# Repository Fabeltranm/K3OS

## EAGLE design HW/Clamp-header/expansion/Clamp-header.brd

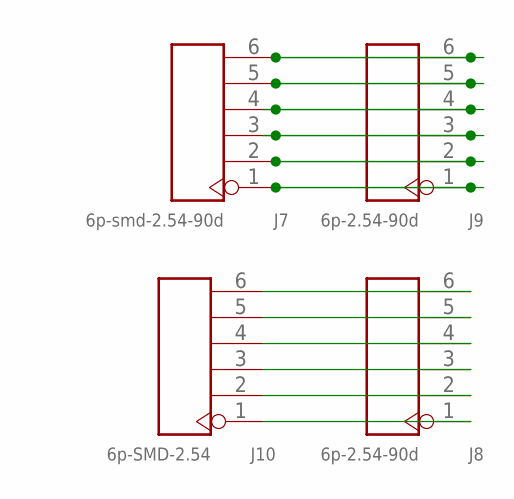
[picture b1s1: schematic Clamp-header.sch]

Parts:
J7: 6p-smd-2.54-90d; H6-SMD-MALE-2.54-90D
J8, J9: 6p-2.54-90d; H6-2.54-90D-FEMALE
J10: 6p-SMD-2.54; H6-SMD-2.54

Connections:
unnamed: J7.6, J9.6
unnamed: J7.5, J9.5
unnamed: J7.4, J9.4
unnamed: J7.3, J9.3
unnamed: J7.2, J9.2
unnamed: J7.1, J9.1
unnamed: J8.6, J10.6
unnamed: J8.5, J10.5
unnamed: J8.4, J10.4
unnamed: J8.3, J10.3
unnamed: J8.2, J10.2
unnamed: J8.1, J10.1

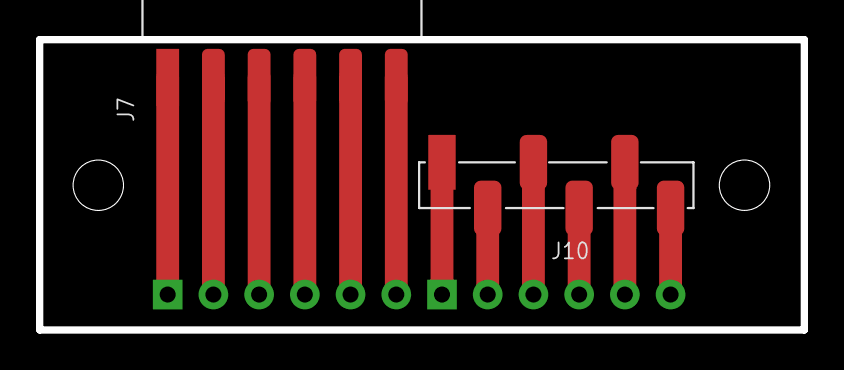
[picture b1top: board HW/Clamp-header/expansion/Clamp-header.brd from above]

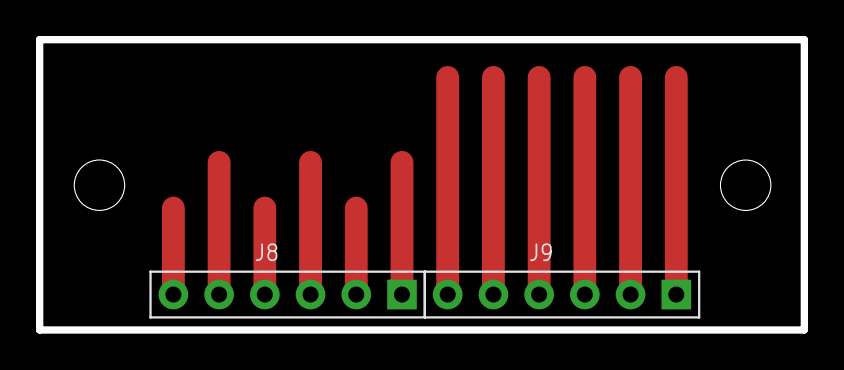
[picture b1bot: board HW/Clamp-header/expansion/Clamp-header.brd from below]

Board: 2 copper layers, 42.5 x 16.1 mm, 4 parts (2 on the bottom side), 12 nets.

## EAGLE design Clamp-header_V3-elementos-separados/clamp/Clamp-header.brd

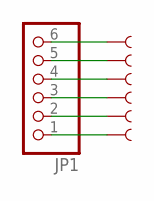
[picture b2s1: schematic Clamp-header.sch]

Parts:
JP1: PINHD-1X6/90; 1X06/90
U$1, U$2, U$3, U$5, U$6, U$7: SEWTAP1; SEWTAP

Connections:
unnamed: JP1.6, U$3.1
unnamed: JP1.5, U$6.1
unnamed: JP1.4, U$7.1
unnamed: JP1.3, U$1.1
unnamed: JP1.2, U$5.1
unnamed: JP1.1, U$2.1

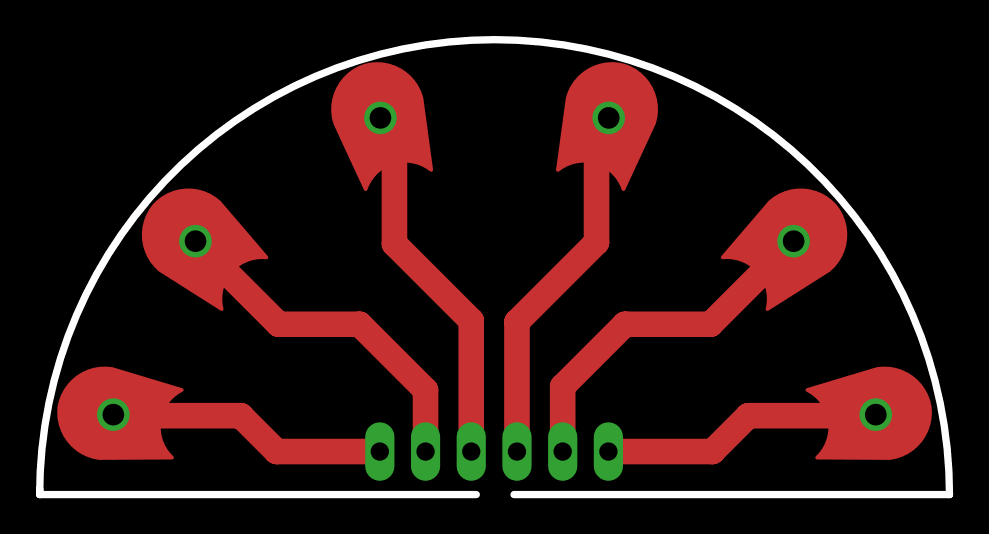
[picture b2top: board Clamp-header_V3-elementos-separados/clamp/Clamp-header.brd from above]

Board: 2 copper layers, 50.5 x 25.3 mm, 7 parts (1 on the bottom side), 6 nets.

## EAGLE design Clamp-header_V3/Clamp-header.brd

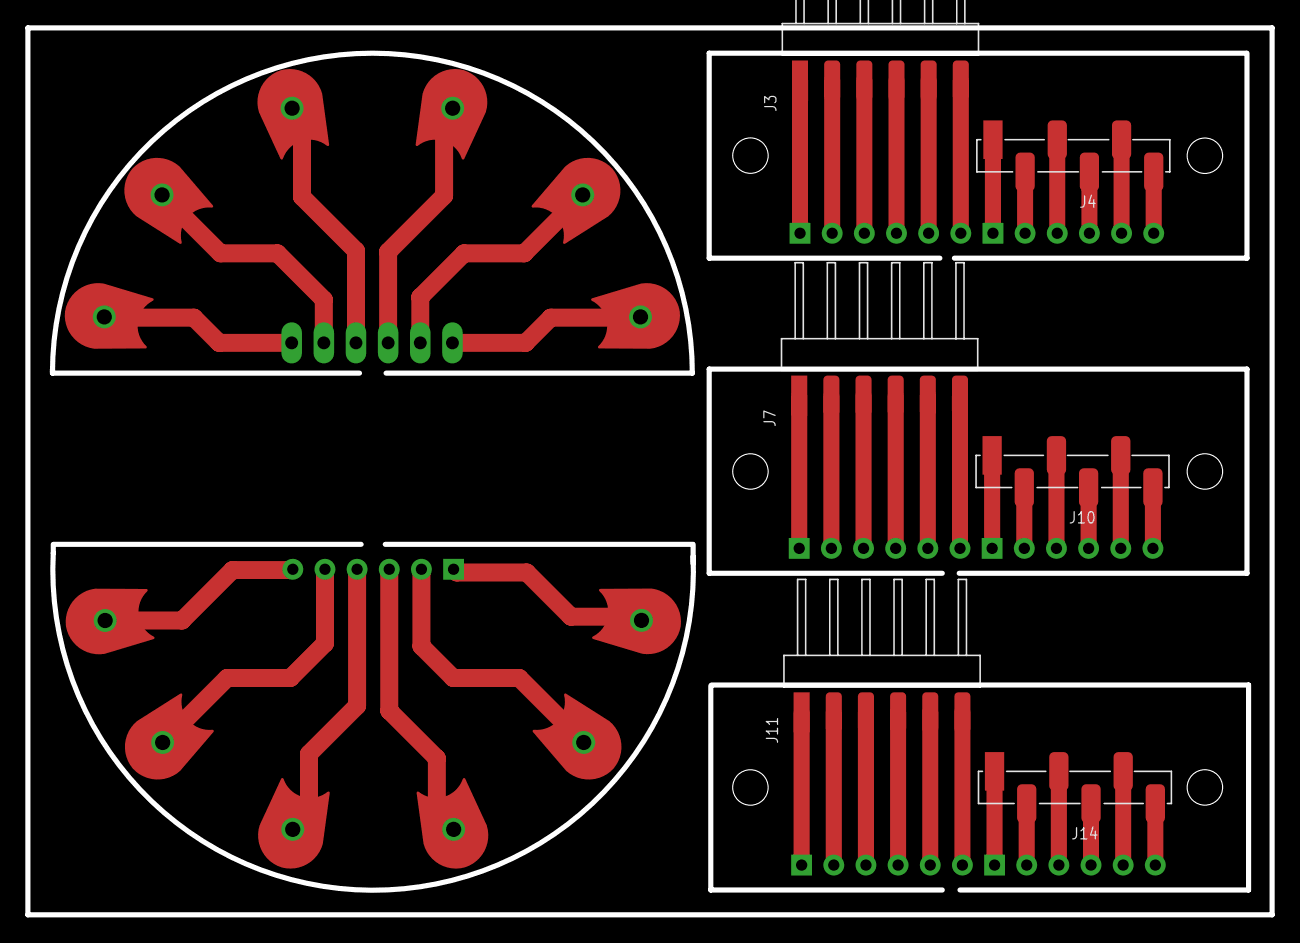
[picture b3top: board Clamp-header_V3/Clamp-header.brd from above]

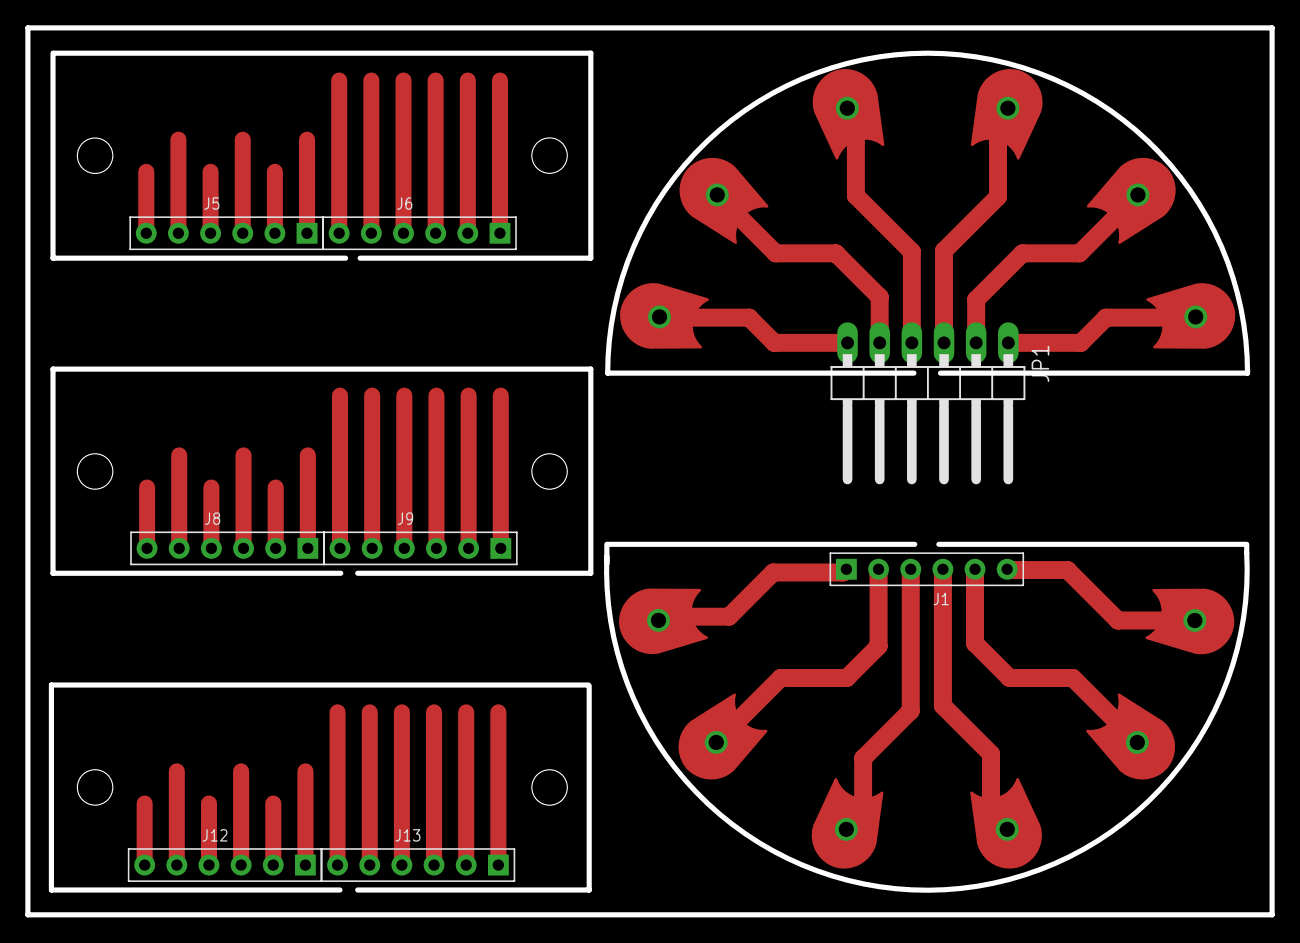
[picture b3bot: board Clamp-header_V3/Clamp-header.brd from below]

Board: 2 copper layers, 98.3 x 70.1 mm, 26 parts (8 on the bottom side), 48 nets.

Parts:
J1, J5, J6, J8, J9, J12, J13: 6p-2.54-90d; H6-2.54-90D-FEMALE
J3, J7, J11: 6p-smd-2.54-90d; H6-SMD-MALE-2.54-90D
J4, J10, J14: 6p-SMD-2.54; H6-SMD-2.54
JP1: 1X06/90
U$1, U$2, U$3, U$4, U$5, U$6, U$7, U$35, U$37, U$39, U$41, U$51: SEWTAP1; SEWTAP

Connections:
unnamed: J1.6, U$51.1
unnamed: J1.5, U$41.1
unnamed: J1.4, U$35.1
unnamed: J1.3, U$37.1
unnamed: J1.2, U$39.1
unnamed: J1.1, U$4.1
unnamed: JP1.6, U$3.1
unnamed: JP1.5, U$6.1
unnamed: JP1.4, U$7.1
unnamed: JP1.3, U$1.1
unnamed: JP1.2, U$5.1
unnamed: JP1.1, U$2.1
unnamed: J3.6, J6.6
unnamed: J3.5, J6.5
unnamed: J3.4, J6.4
unnamed: J3.3, J6.3
unnamed: J3.2, J6.2
unnamed: J3.1, J6.1
unnamed: J4.6, J5.6
unnamed: J4.5, J5.5
unnamed: J4.4, J5.4
unnamed: J4.3, J5.3
unnamed: J4.2, J5.2
unnamed: J4.1, J5.1
unnamed: J7.6, J9.6
unnamed: J7.5, J9.5
unnamed: J7.4, J9.4
unnamed: J7.3, J9.3
unnamed: J7.2, J9.2
unnamed: J7.1, J9.1
unnamed: J8.6, J10.6
unnamed: J8.5, J10.5
unnamed: J8.4, J10.4
unnamed: J8.3, J10.3
unnamed: J8.2, J10.2
unnamed: J8.1, J10.1
unnamed: J11.6, J13.6
unnamed: J11.5, J13.5
unnamed: J11.4, J13.4
unnamed: J11.3, J13.3
unnamed: J11.2, J13.2
unnamed: J11.1, J13.1
unnamed: J12.6, J14.6
unnamed: J12.5, J14.5
unnamed: J12.4, J14.4
unnamed: J12.3, J14.3
unnamed: J12.2, J14.2
unnamed: J12.1, J14.1

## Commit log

2017-03-23 V0.9
2017-03-23 v1.0
2017-03-23 model 3d
2017-04-08 RPi Hat V2
2017-04-22 include logos
2017-04-22 gerber
2017-04-22 delated p
2017-04-26 cambios en clamp
    modificacion V2 al clamp
2017-04-26 Revert "cambios en clamp"
    This reverts commit a5dcf231417c90a1c8c8961c6481be991a881ba8.
2017-04-26 modificacion gerber clamp
2017-04-26 subida de archivos V2
2017-04-26 Add files via upload
    resubida de archivo con cambio en el diametro de un orificio
2017-04-28 Nueva version con el header alineado al centro
2017-04-28 actualizacion con ambas board separadas
2017-05-02 cambios en los gerber de la tarjeta expansion
2017-05-03 cambios en la board de expansion RPI
2017-05-03 cambios RPI board
2017-05-03 cambios en los archivos gerber de la tarjeta RPI
2017-05-03 Cambios de la PCB
2017-05-04 cambios en la RPI expansion board y logos
2017-05-04 drill
2017-05-04 cambiops
2017-05-04 cambios
2017-05-04 cambios en archivos gerber de la expansion RPI
2017-05-04 cambios en los gerber de la RPI expansion
2017-05-04 cambios Gerber RPI expansion
2017-05-05 cambios en tarjeta clamp
2017-05-05 ajuste
2017-05-16 Update readme.m and example
2017-05-23 cambios gerber k3
2017-05-23 ejemplo foto para RPI con Ultrasonido
2017-06-02 add pro
2017-06-20 Update cabezote
2017-07-10 cofig files and dir
2017-07-10 config dir and files
2017-07-10 Ultimas modificaciones en los archivos gerber de tarjeta CLAMP
2017-07-12 add audio
2017-07-31 add planos finales de corte laser
2017-11-20 Se agrega PCB para MIC I2S SPH0645LM4H-B
2018-04-07 imagen fondo de pantalla para k3os
2018-07-03 nuevo diseño 1.1
